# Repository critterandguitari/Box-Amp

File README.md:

Box-Amp
=======

3W audio amp.  Power form 9VDC.

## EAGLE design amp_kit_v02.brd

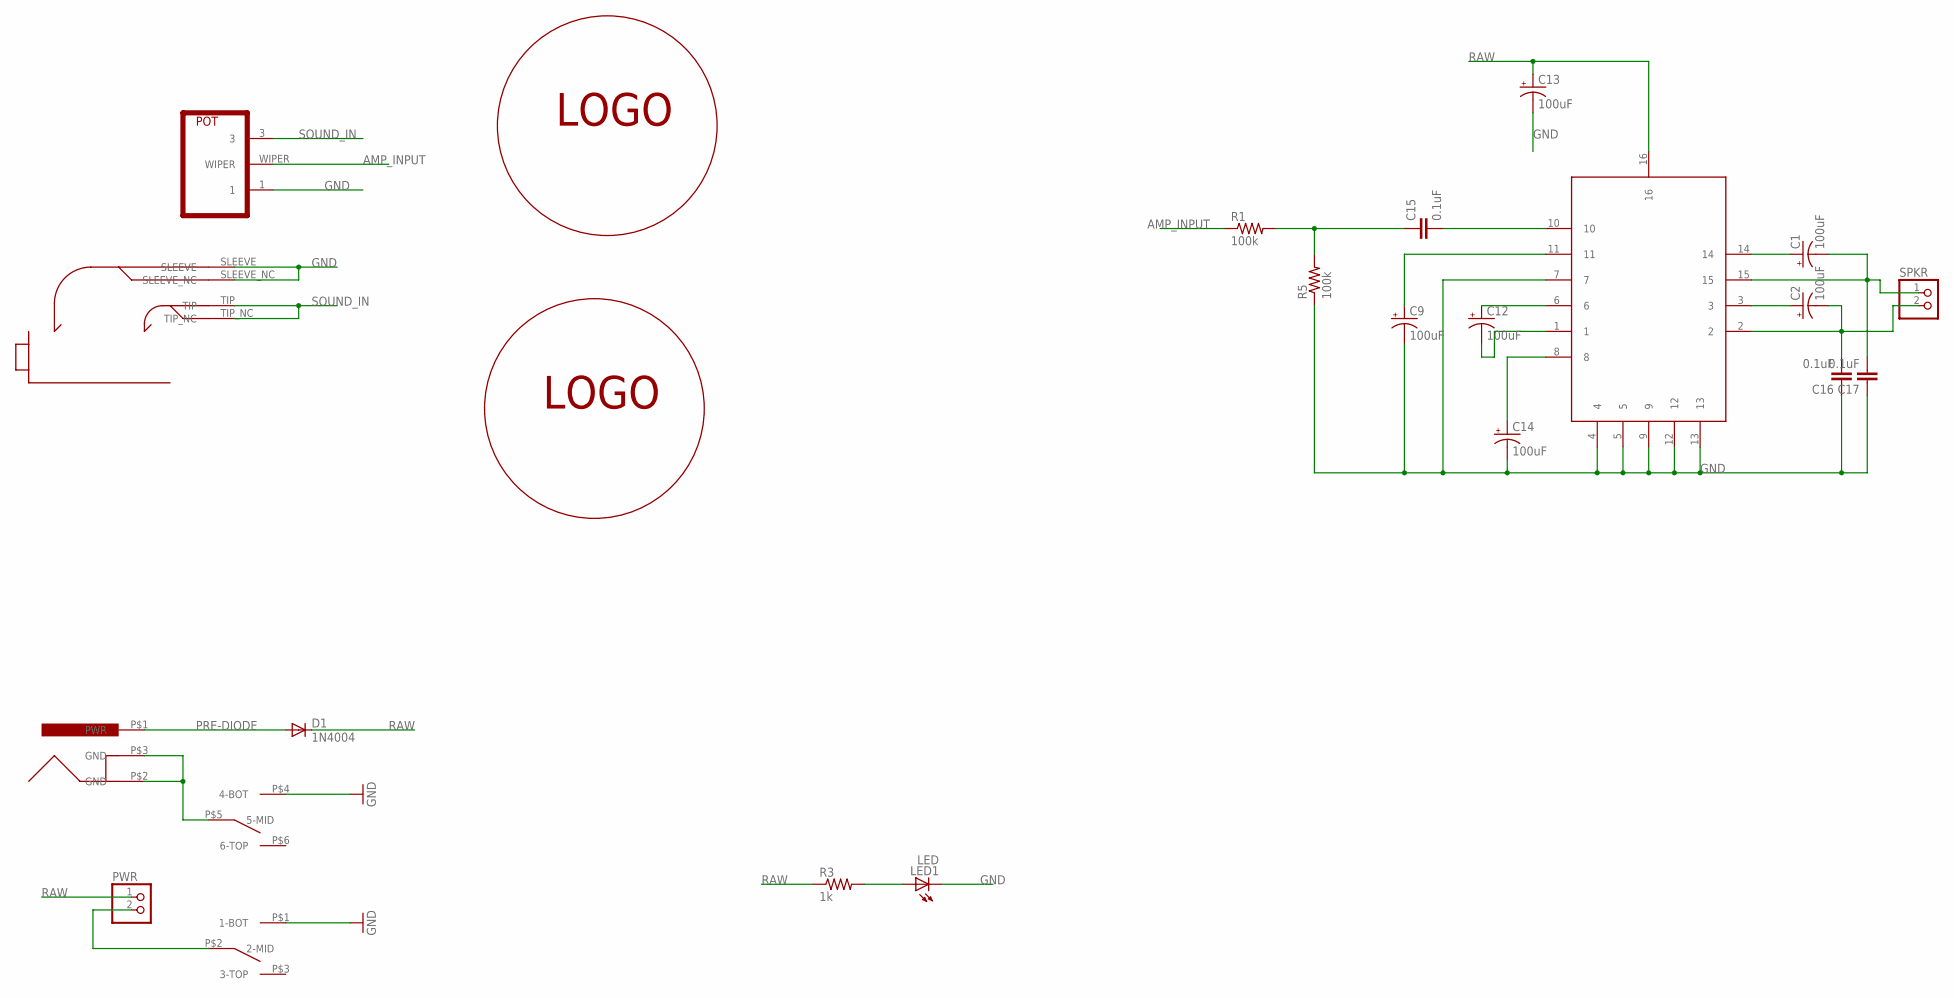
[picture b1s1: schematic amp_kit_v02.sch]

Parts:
C1, C2, C9, C12, C13, C14: 100uF; E2,5-7
C15, C16, C17: 0.1uF; C025-025X050
D1: 1N4004; DO41-10
LED1: LED; LED5MM
PWR: PINHD-1X2; 1X02
R1, R5: 100k; 0204V
R3: 1k; 0207/10
SPKR: PINHD-1X2; 1X02
U$1: TEA2025; DIL16
U$2, U$7: LOGOCG; LOGO-CG
U$3: POT_BOX_AMP
U$4: PUSHPOWER
U$5: POWER_JACK
U$6: MONO_PHONE

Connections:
AMP_INPUT: R1.1, U$3.WIPER
GND: C9.-, C13.-, C14.-, C16.1, C17.1, LED1.K (C), R5.1, U$1.4, U$1.5, U$1.7, U$1.9, U$1.12, U$1.13, U$3.1, U$4.P$1 (1-BOT), U$4.P$4 (4-BOT), U$6.SLEEVE, U$6.SLEEVE_NC
unnamed: PWR.2, U$4.P$2 (2-MID)
unnamed: LED1.A, R3.2
unnamed: C14.+, U$1.8
unnamed: C12.-, U$1.1
unnamed: U$4.P$5 (5-MID), U$5.P$2 (GND), U$5.P$3 (GND)
unnamed: C12.+, U$1.6
unnamed: C9.+, U$1.11
unnamed: C2.-, C16.2, SPKR.2, U$1.2
unnamed: C15.2, U$1.10
unnamed: C1.+, U$1.14
unnamed: C2.+, U$1.3
unnamed: C1.-, C17.2, SPKR.1, U$1.15
unnamed: C15.1, R1.2, R5.2
PRE-DIODE: D1.A, U$5.P$1 (PWR)
RAW: C13.+, D1.C, PWR.1, R3.1, U$1.16
SOUND_IN: U$3.3, U$6.TIP, U$6.TIP_NC

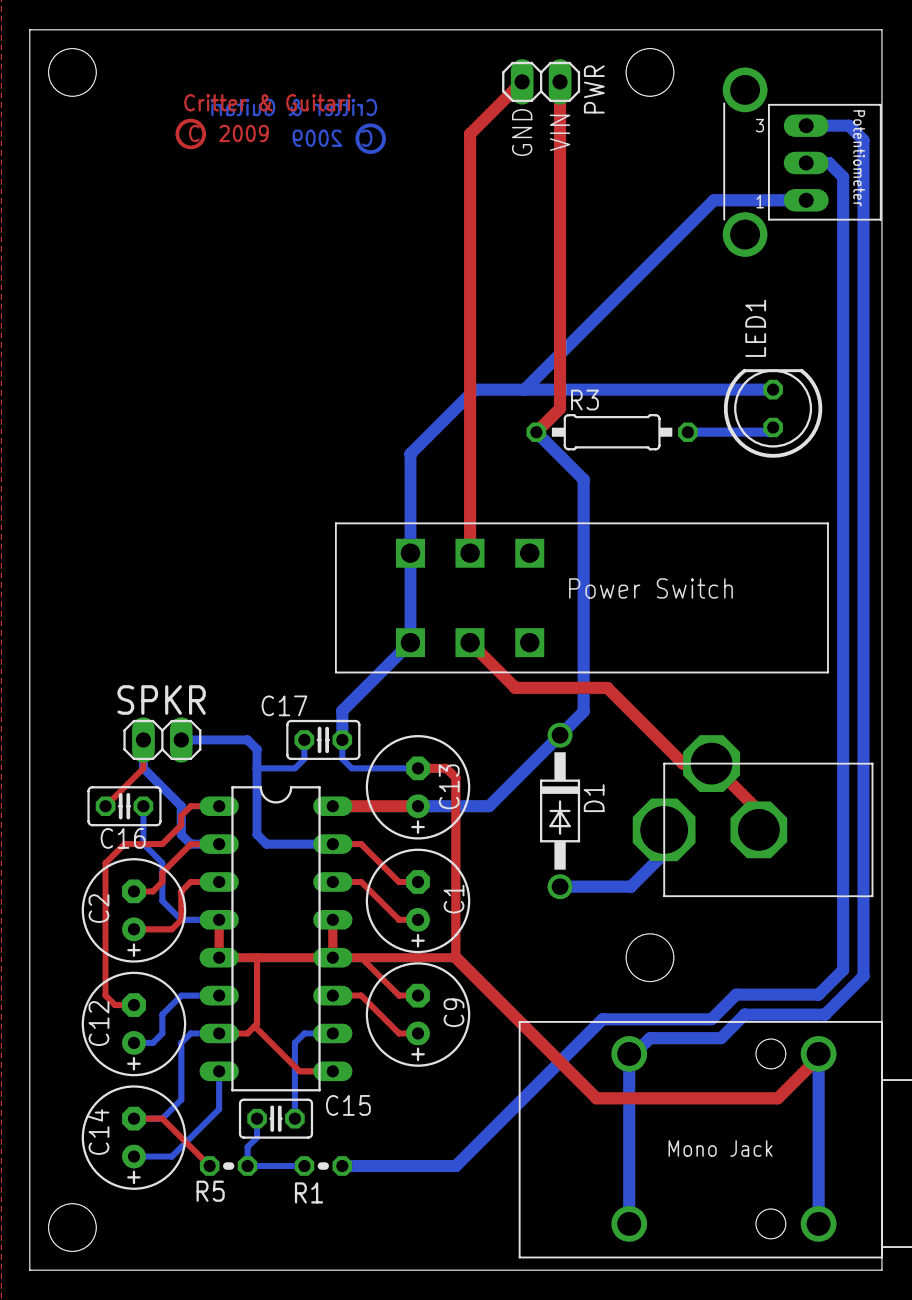
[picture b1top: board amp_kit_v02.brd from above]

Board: 2 copper layers, 57.1 x 83.2 mm, 23 parts (1 on the bottom side), 18 nets.

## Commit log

2013-04-21 adding eagle files
2013-04-22 readme
